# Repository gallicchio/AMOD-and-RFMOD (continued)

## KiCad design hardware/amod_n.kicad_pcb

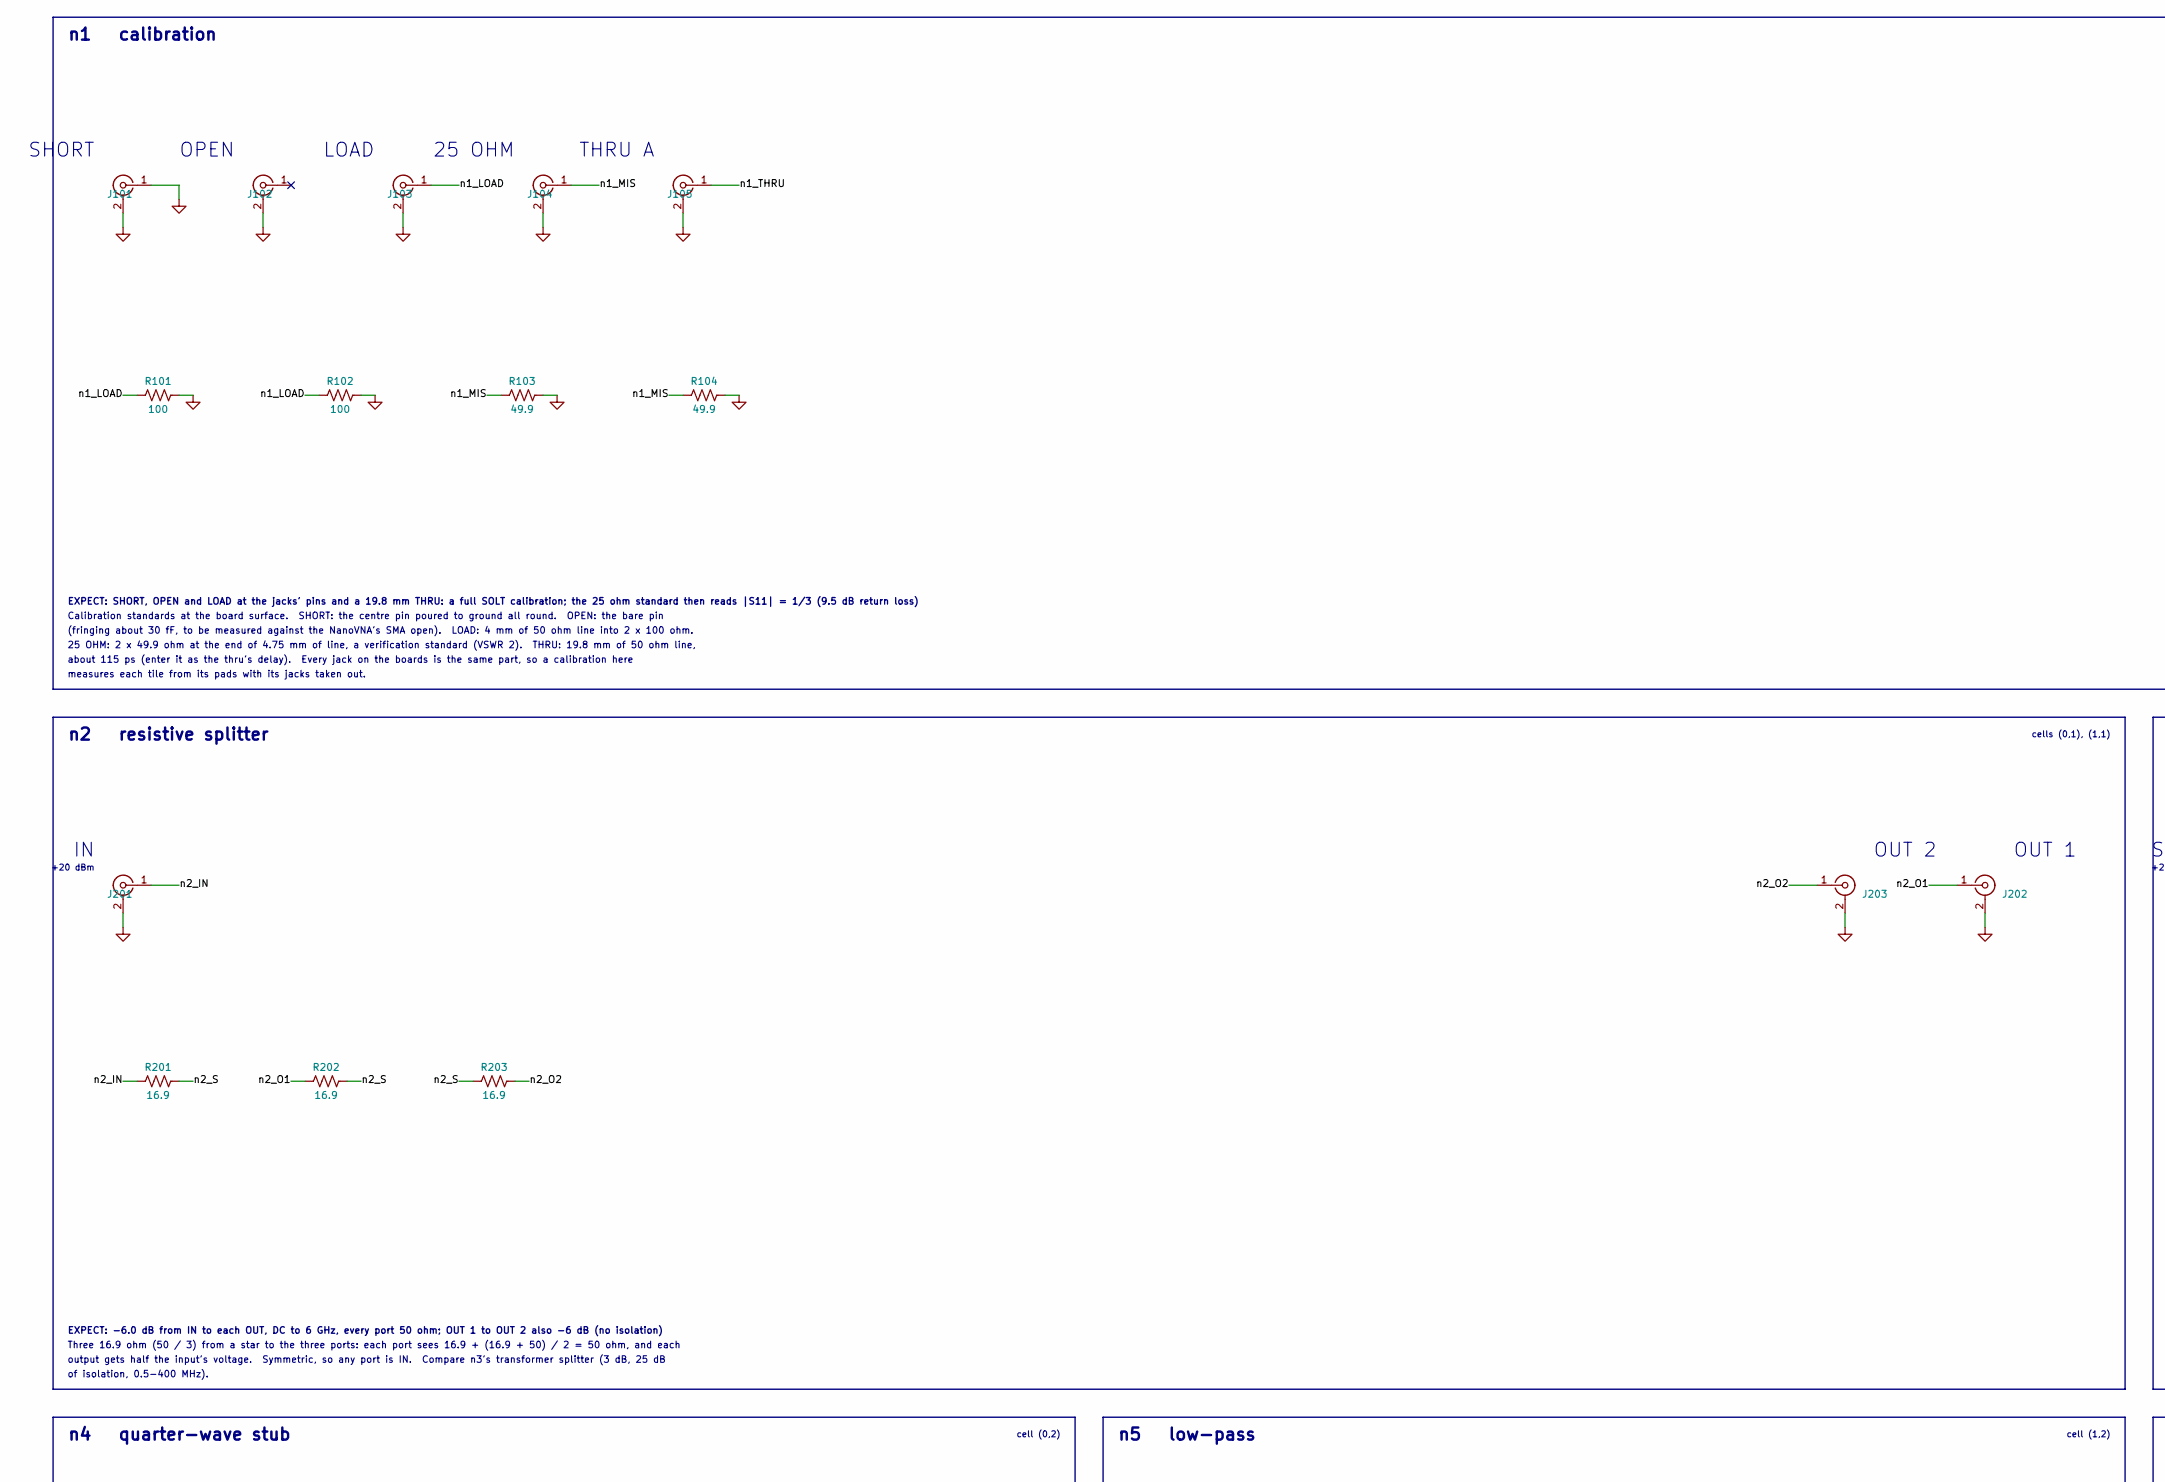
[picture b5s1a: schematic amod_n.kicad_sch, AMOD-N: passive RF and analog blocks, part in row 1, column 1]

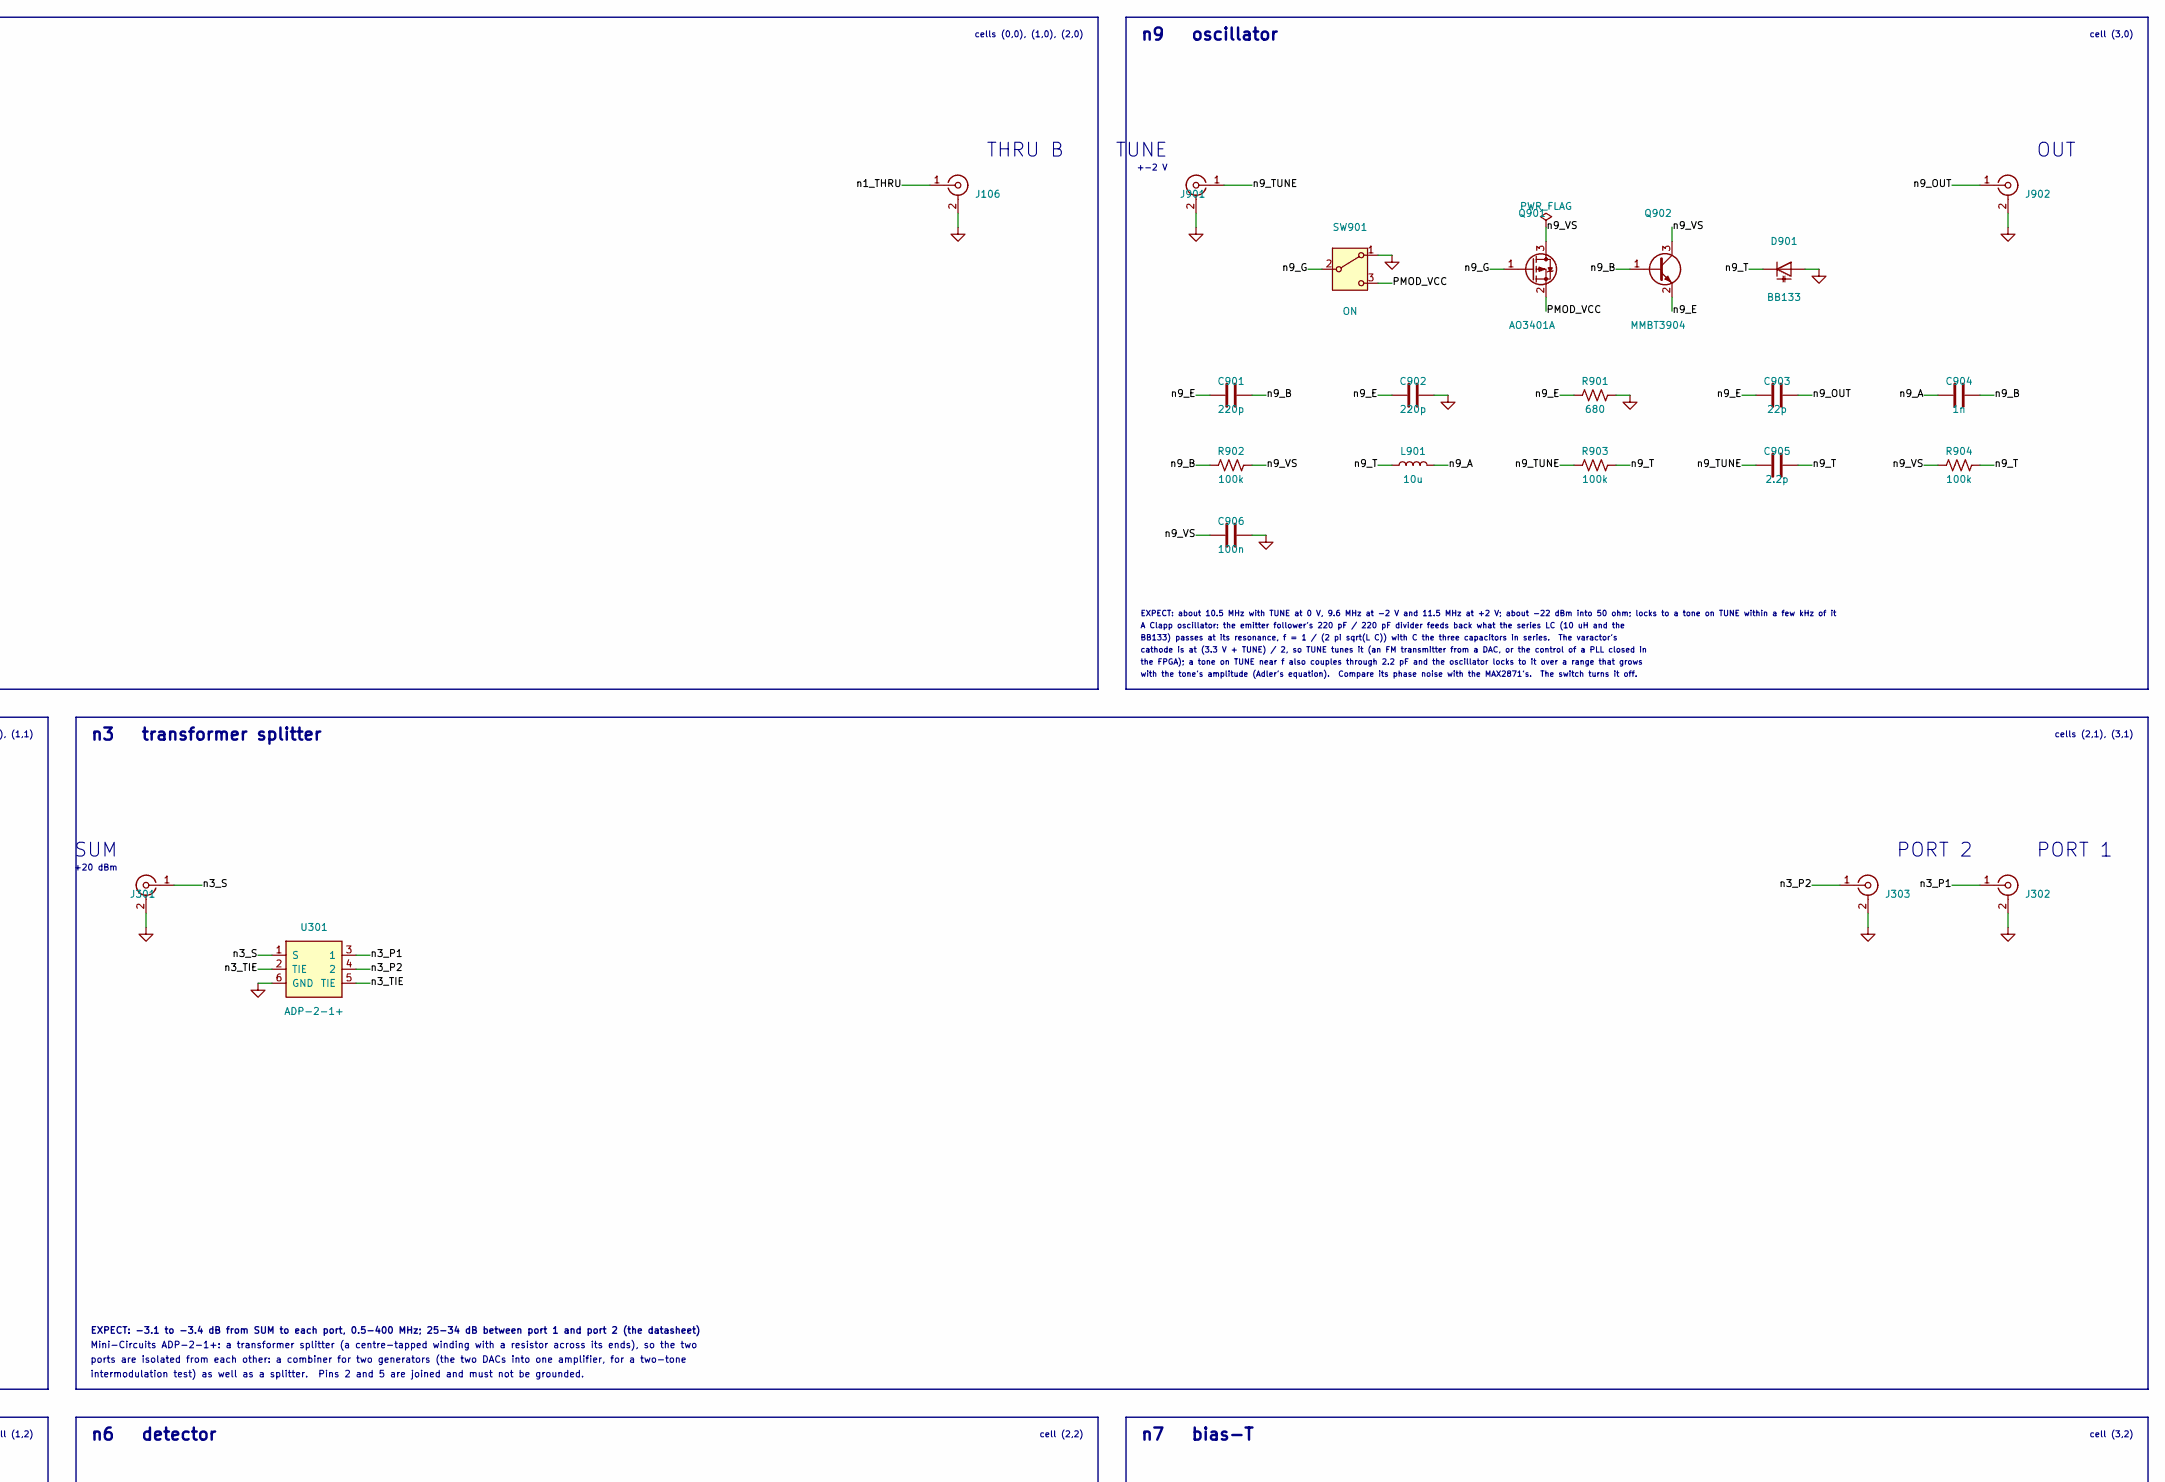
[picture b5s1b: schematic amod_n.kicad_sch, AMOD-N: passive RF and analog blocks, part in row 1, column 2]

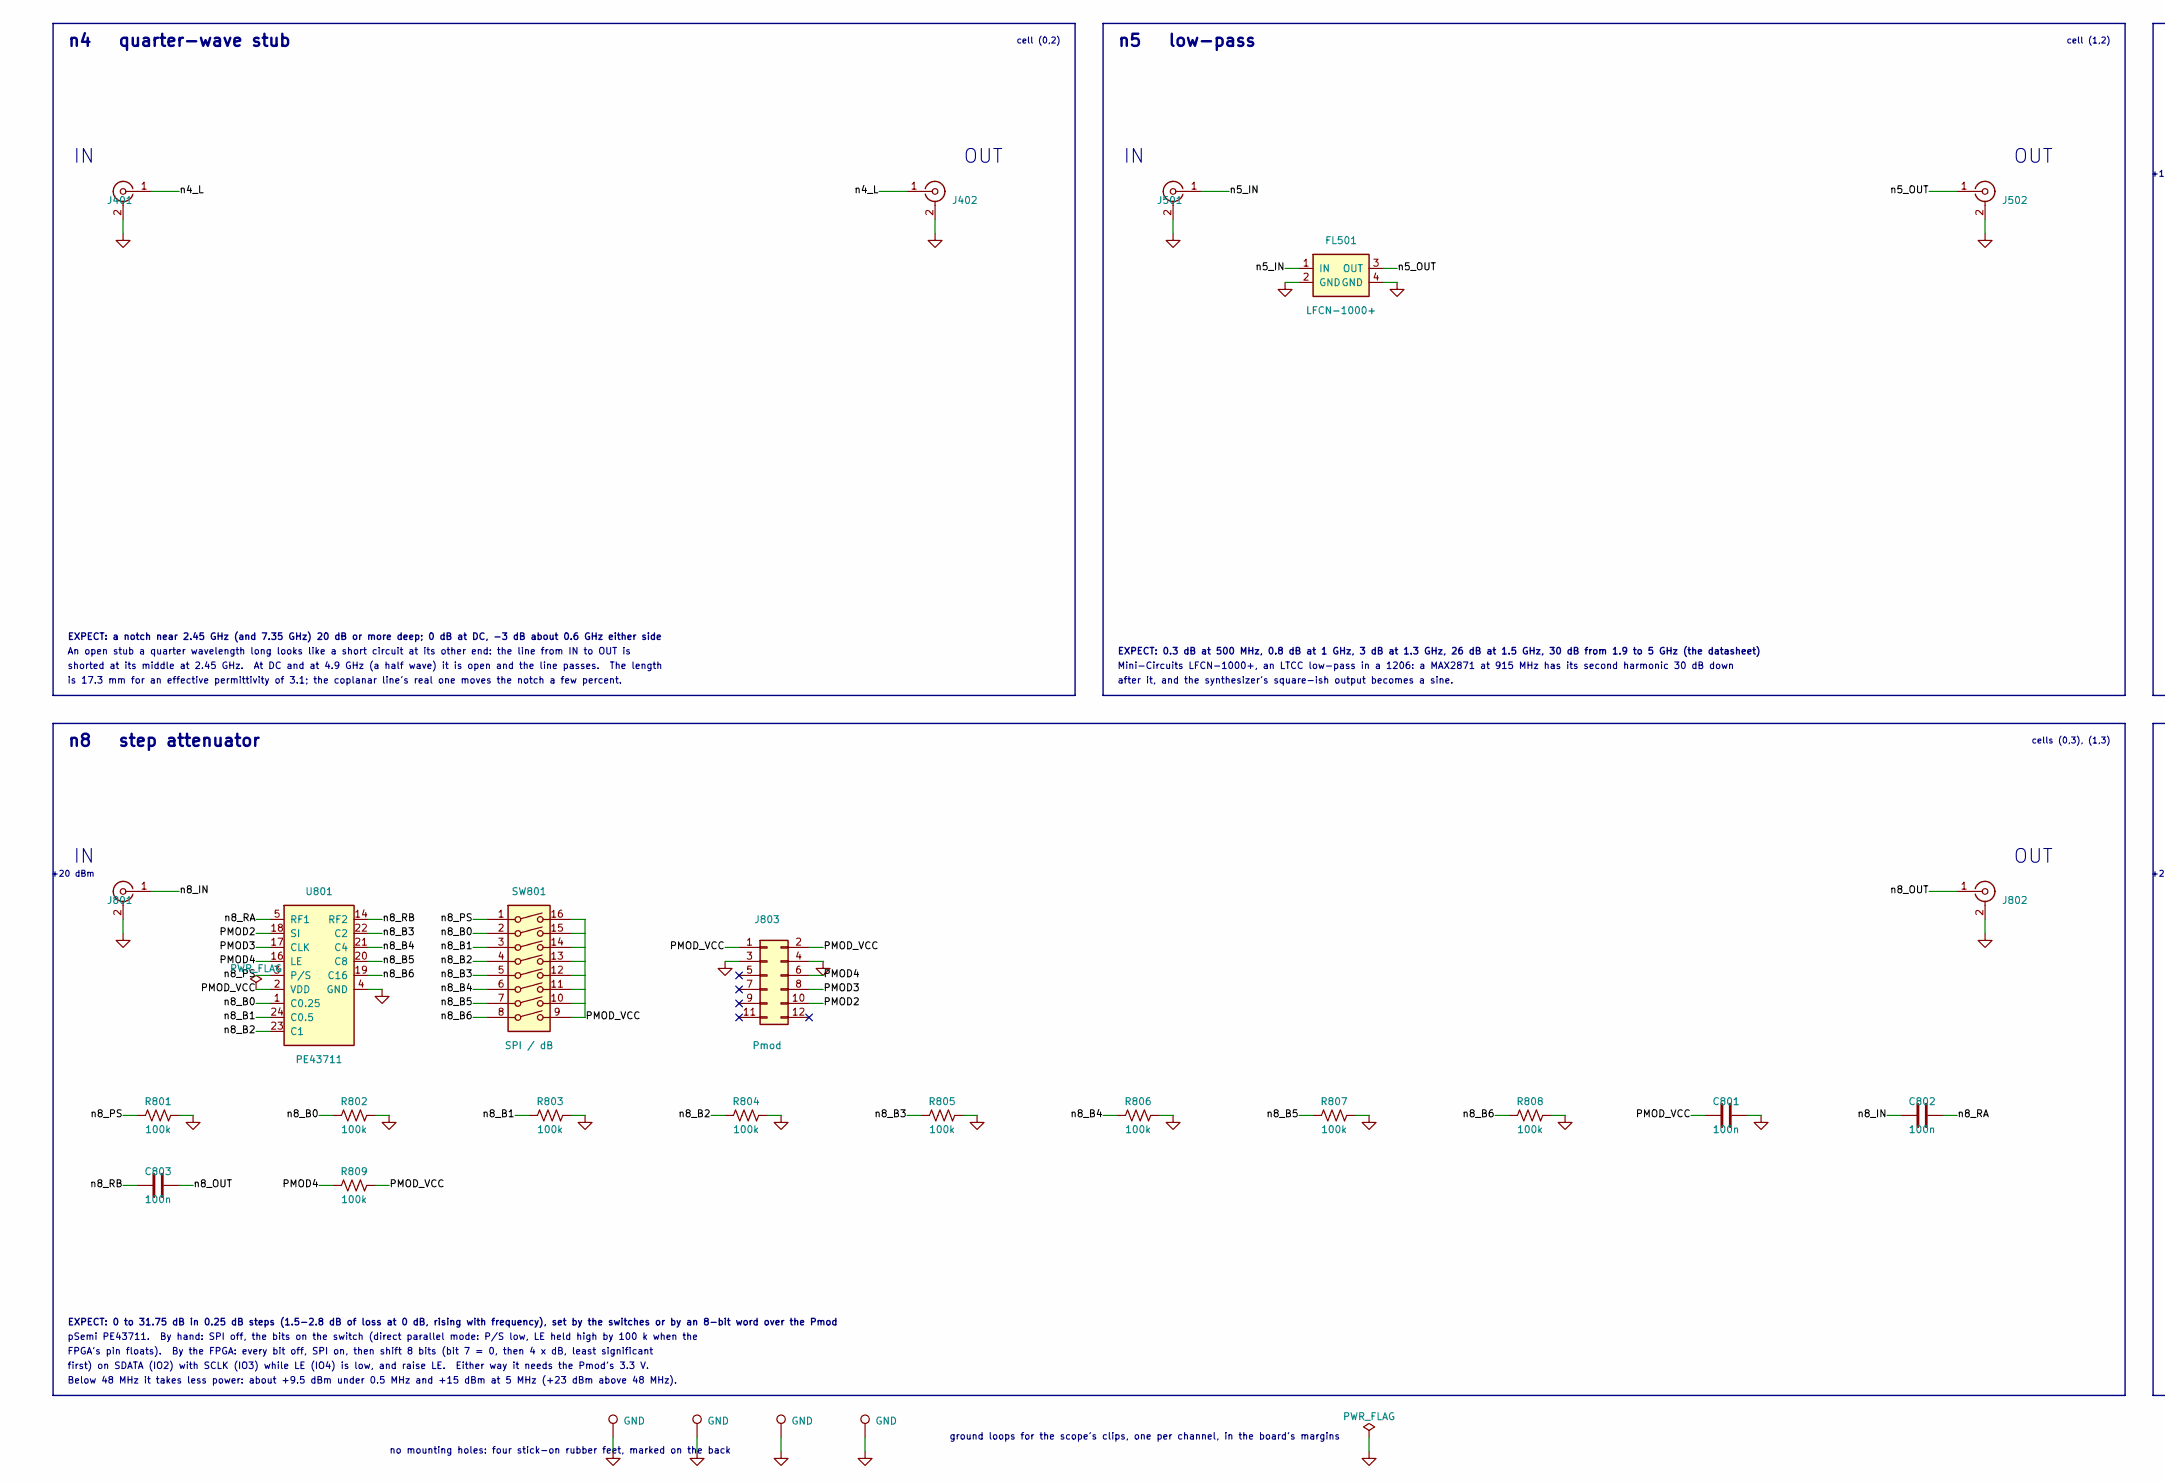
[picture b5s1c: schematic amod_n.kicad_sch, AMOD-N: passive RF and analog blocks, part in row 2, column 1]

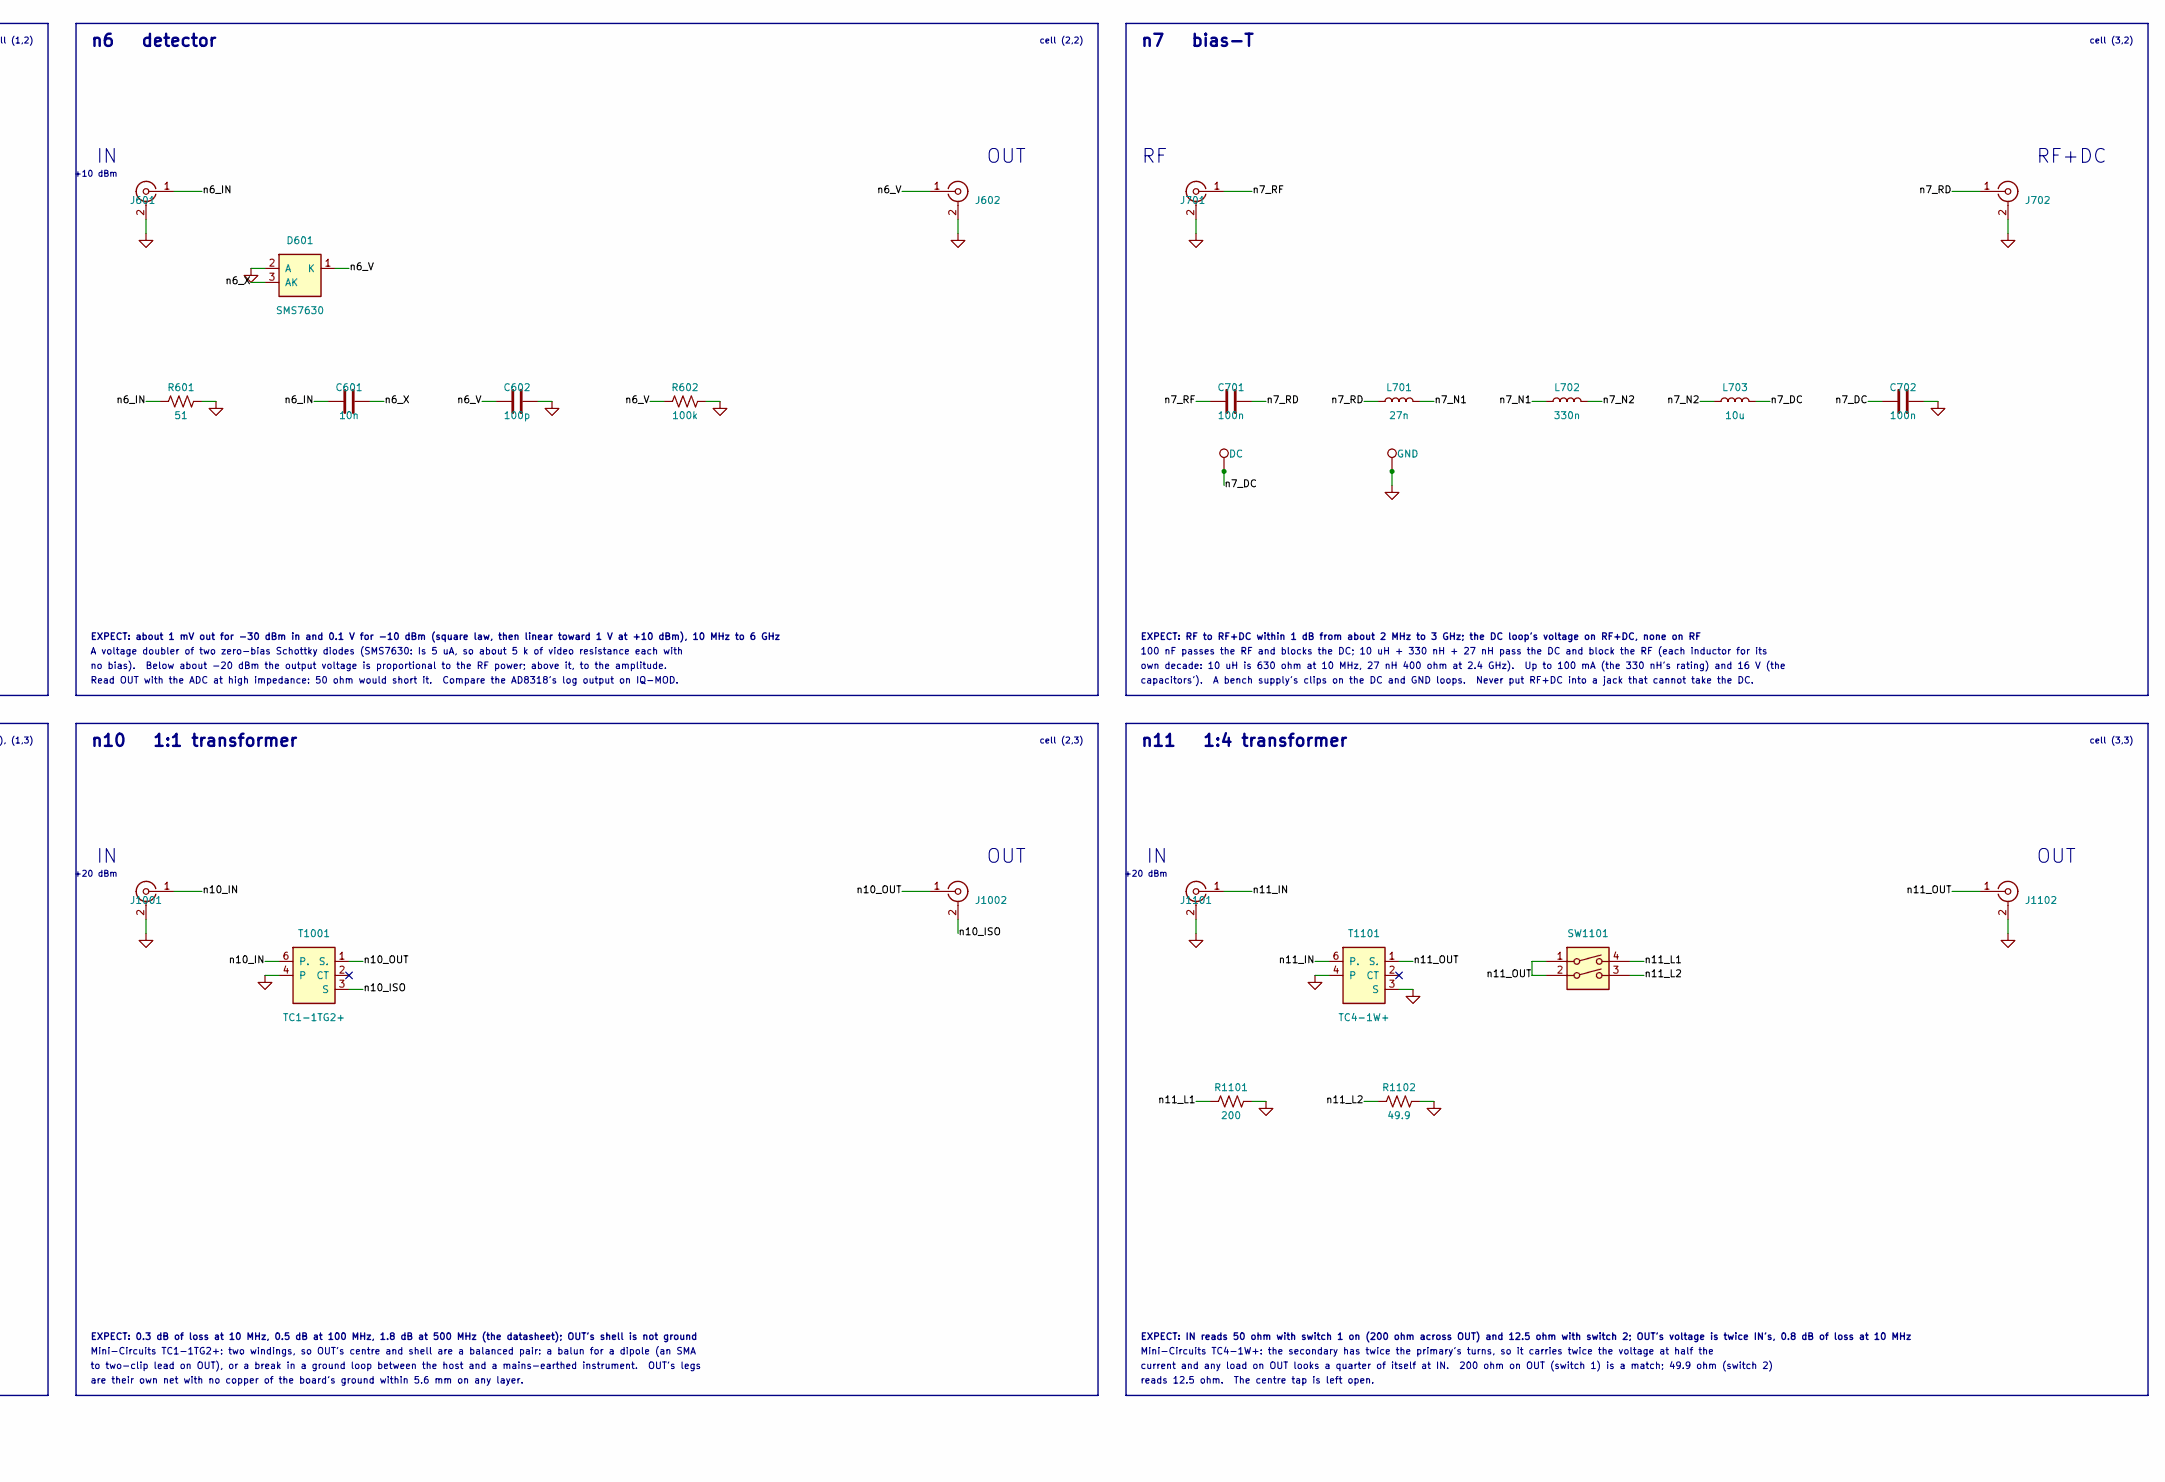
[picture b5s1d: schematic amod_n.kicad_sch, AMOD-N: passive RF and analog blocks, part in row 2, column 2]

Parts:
C601: 10n; C_0402_1005Metric; MPN CL05B103KB5NNNC; LCSC C15195
C602: 100p; C_0402_1005Metric; MPN 0402CG101J500NT; LCSC C1546
C701, C702, C801, C802, C803, C906: 100n; C_0402_1005Metric; MPN CL05B104KO5NNNC; LCSC C1525
C901, C902: 220p; C_0402_1005Metric; MPN 0402CG221J500NT; LCSC C39122
C903: 22p; C_0402_1005Metric; MPN 0402CG220J500NT; LCSC C1555
C904: 1n; C_0402_1005Metric; MPN 0402B102K500NT; LCSC C1523
C905: 2.2p; C_0402_1005Metric; MPN 0402CG2R2C500NT; LCSC C1559
D601: SMS7630; SOT-23; MPN SMS7630-006LF; LCSC C6489012
D901: BB133; D_SOD-323; MPN BB133; LCSC C5334579
FL501: LFCN-1000+; Filter_LTCC_1206_LFCN; MPN LFCN-1000+; LCSC C879868
J101, J102, J103, J104, J105, J106, J201, J202, J203, J301, J302, J303, J401, J402, J501, J502, J601, J602, J701, J702, J801, J802, J901, J902, J1001, J1002, J1101, J1102: SMA; SMA_BWSMA-KE-Z001_Vertical; MPN BWSMA-KE-Z001; LCSC C496549
J803: Pmod; PinHeader_2x06_P2.54mm_Horizontal_PZ254R-12-12P; MPN PZ254R-12-12P; LCSC C492434
L701: 27n; L_0402_1005Metric; MPN LQW15AN27NG80D; LCSC C882469
L702: 330n; L_0603_1608Metric; MPN CS0603-R33J-S; LCSC C142165
L703, L901: 10u; L_1210_3225Metric; MPN NLV32T-100J-PF; LCSC C76835
Q901: AO3401A; SOT-23; MPN AO3401A; LCSC C15127
Q902: MMBT3904; SOT-23; MPN MMBT3904(RANGE:100-300); LCSC C20526
R101, R102: 100; R_0402_1005Metric; MPN 0402WGF1000TCE; LCSC C25076
R103, R104, R1102: 49.9; R_0402_1005Metric; MPN CRCW040249R9FKEDHP; LCSC C844112
R201, R202, R203: 16.9; R_0402_1005Metric; MPN 0402WGF169JTCE; LCSC C82287
R601: 51; R_0402_1005Metric; MPN 0402WGF510JTCE; LCSC C25125
R602, R801, R802, R803, R804, R805, R806, R807, R808, R809, R902, R903, R904: 100k; R_0402_1005Metric; MPN 0402WGF1003TCE; LCSC C25741
R901: 680; R_0402_1005Metric; MPN 0402WGF6800TCE; LCSC C25130
R1101: 200; R_0402_1005Metric; MPN 0402WGF2000TCE; LCSC C25087
SW801: SPI / dB; SW_DIP_SPSTx08_Slide_1.27mm_DSHP08; MPN DSHP08TSGET; LCSC C40738
SW901: ON; SW_SPDT_Shouhan_MSK12C02; MPN MSK12C02; LCSC C431540
SW1101: LOAD; SW_DIP_SPSTx02_Slide_1.27mm_DSHP02; MPN DSHP02TSGET; LCSC C40735
T1001: TC1-1TG2+; MiniCircuits_AT224_5P; MPN TC1-1TG2+; LCSC C3305009
T1101: TC4-1W+; MiniCircuits_AT224_5P; MPN TC4-1W+; LCSC C879855
TP701: DC; TestPoint_Loop_RH-5019; MPN RH-5019; LCSC C5199800
TP702, TP9901, TP9902, TP9903, TP9904: GND; TestPoint_Loop_RH-5019; MPN RH-5019; LCSC C5199800
U301: ADP-2-1+; MiniCircuits_CD636_ADP-2-1; MPN ADP-2-1+; LCSC C2683460
U801: PE43711; QFN-24-1EP_4x4mm_P0.5mm_EP2.7x2.7mm; MPN PE43711B-Z; LCSC C470929

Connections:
/PMOD2: J803.10, U801.18 (SI)
/PMOD3: J803.8, U801.17 (CLK)
/PMOD4: J803.6, R809.1, U801.16 (LE)
/PMOD_VCC: C801.1, J803.1, J803.2, Q901.2 (S), R809.2, SW801.9, SW801.10, SW801.11, SW801.12, SW801.13, SW801.14, SW801.15, SW801.16, SW901.3 (C), U801.2 (VDD)
/n1_LOAD: J103.1 (In), R101.1, R102.1
/n1_MIS: J104.1 (In), R103.1, R104.1
/n1_THRU: J105.1 (In), J106.1 (In)
/n2_IN: J201.1 (In), R201.1
/n2_O1: J202.1 (In), R202.1
/n2_O2: J203.1 (In), R203.2
/n2_S: R201.2, R202.2, R203.1
/n3_P1: J302.1 (In), U301.3 (1)
/n3_P2: J303.1 (In), U301.4 (2)
/n3_S: J301.1 (In), U301.1 (S)
/n3_TIE: U301.2 (TIE), U301.5 (TIE)
/n4_L: J401.1 (In), J402.1 (In)
/n5_IN: FL501.1 (IN), J501.1 (In)
/n5_OUT: FL501.3 (OUT), J502.1 (In)
/n6_IN: C601.1, J601.1 (In), R601.1
/n6_V: C602.1, D601.1 (K), J602.1 (In), R602.1
/n6_X: C601.2, D601.3 (AK)
/n7_DC: C702.1, L703.2, TP701.1
/n7_N1: L701.2, L702.1
/n7_N2: L702.2, L703.1
/n7_RD: C701.2, J702.1 (In), L701.1
/n7_RF: C701.1, J701.1 (In)
/n8_B0: R802.1, SW801.2, U801.1 (C0.25)
/n8_B1: R803.1, SW801.3, U801.24 (C0.5)
/n8_B2: R804.1, SW801.4, U801.23 (C1)
/n8_B3: R805.1, SW801.5, U801.22 (C2)
/n8_B4: R806.1, SW801.6, U801.21 (C4)
/n8_B5: R807.1, SW801.7, U801.20 (C8)
/n8_B6: R808.1, SW801.8, U801.19 (C16)
/n8_IN: C802.1, J801.1 (In)
/n8_OUT: C803.2, J802.1 (In)
/n8_PS: R801.1, SW801.1, U801.3 (P/S)
/n8_RA: C802.2, U801.5 (RF1)
/n8_RB: C803.1, U801.14 (RF2)
/n9_A: C904.1, L901.2
/n9_B: C901.2, C904.2, Q902.1 (B), R902.1
/n9_E: C901.1, C902.1, C903.1, Q902.2 (E), R901.1
/n9_G: Q901.1 (G), SW901.2 (B)
/n9_OUT: C903.2, J902.1 (In)
/n9_T: C905.2, D901.1 (K), L901.1, R903.2, R904.2
/n9_TUNE: C905.1, J901.1 (In), R903.1
/n9_VS: C906.1, Q901.3 (D), Q902.3 (C), R902.2, R904.1
/n10_IN: J1001.1 (In), T1001.6 (P.)
/n10_ISO: J1002.2 (Ext), T1001.3 (S)
/n10_OUT: J1002.1 (In), T1001.1 (S.)
/n11_IN: J1101.1 (In), T1101.6 (P.)
/n11_L1: R1101.1, SW1101.4
/n11_L2: R1102.1, SW1101.3
/n11_OUT: J1102.1 (In), SW1101.1, SW1101.2, T1101.1 (S.)
GND: C602.2, C702.2, C801.2, C902.2, C906.2, D601.2 (A), D901.2 (A), FL501.2 (GND), FL501.4 (GND), J101.1 (In), J101.2 (Ext), J102.2 (Ext), J103.2 (Ext), J104.2 (Ext), J105.2 (Ext), J106.2 (Ext), J201.2 (Ext), J202.2 (Ext), J203.2 (Ext), J301.2 (Ext), J302.2 (Ext), J303.2 (Ext), J401.2 (Ext), J402.2 (Ext), J501.2 (Ext), J502.2 (Ext), J601.2 (Ext), J602.2 (Ext), J701.2 (Ext), J702.2 (Ext), J801.2 (Ext), J802.2 (Ext), J803.3, J803.4, J901.2 (Ext), J902.2 (Ext), J1001.2 (Ext), J1101.2 (Ext), J1102.2 (Ext), R101.2, R102.2, R103.2, R104.2, R601.2, R602.2, R801.2, R802.2, R803.2, R804.2, R805.2, R806.2, R807.2, R808.2, R901.2, R1101.2, R1102.2, SW901.1 (A), T1001.4, T1101.3 (S), T1101.4, TP702.1, TP9901.1, TP9902.1, TP9903.1, TP9904.1, U301.6 (GND), U801.4 (GND), U801.6 (GND), U801.7 (GND), U801.8 (GND), U801.9 (GND), U801.10 (GND), U801.11 (GND), U801.12 (GND), U801.13 (GND), U801.15 (GND), U801.25 (GND)

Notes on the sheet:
SUM
cells (2,1), (3,1)
EXPECT: -3.1 to -3.4 dB from SUM to each port, 0.5-400 MHz; 25-34 dB between port 1 and port 2 (the datasheet)
OUT
EXPECT: 0.3 dB of loss at 10 MHz, 0.5 dB at 100 MHz, 1.8 dB at 500 MHz (the datasheet); OUT's shell is not ground
EXPECT: 0 to 31.75 dB in 0.25 dB steps (1.5-2.8 dB of loss at 0 dB, rising with frequency), set by the switches or by an 8-bit word over the Pmod
n1 calibration
cells (0,0), (1,0), (2,0)
n3 transformer splitter
cell (0,2)
measures each tile from its pads with its jacks taken out.
RF+DC
25 OHM: 2 x 49.9 ohm at the end of 4.75 mm of line, a verification standard (VSWR 2). THRU: 19.8 mm of 50 ohm line,
n11 1:4 transformer
cell (3,3)
An open stub a quarter wavelength long looks like a short circuit at its other end: the line from IN to OUT is
(fringing about 30 fF, to be measured against the NanoVNA's SMA open). LOAD: 4 mm of 50 ohm line into 2 x 100 ohm.
25 OHM
PORT 2
A voltage doubler of two zero-bias Schottky diodes (SMS7630: Is 5 uA, so about 5 k of video resistance each with
OUT 2
THRU A
+20 dBm
n2 resistive splitter
EXPECT: SHORT, OPEN and LOAD at the jacks' pins and a 19.8 mm THRU: a full SOLT calibration; the 25 ohm standard then reads |S11| = 1/3 (9.5 dB return loss)
LOAD
n8 step attenuator
the FPGA); a tone on TUNE near f also couples through 2.2 pF and the oscillator locks to it over a range that grows
EXPECT: RF to RF+DC within 1 dB from about 2 MHz to 3 GHz; the DC loop's voltage on RF+DC, none on RF
are their own net with no copper of the board's ground within 5.6 mm on any layer.
of isolation, 0.5-400 MHz).
current and any load on OUT looks a quarter of itself at IN. 200 ohm on OUT (switch 1) is a match; 49.9 ohm (switch 2)
EXPECT: a notch near 2.45 GHz (and 7.35 GHz) 20 dB or more deep; 0 dB at DC, -3 dB about 0.6 GHz either side
EXPECT: -6.0 dB from IN to each OUT, DC to 6 GHz, every port 50 ohm; OUT 1 to OUT 2 also -6 dB (no isolation)
no bias). Below about -20 dBm the output voltage is proportional to the RF power; above it, to the amplitude.
n5 low-pass
cell (2,3)
capacitors'). A bench supply's clips on the DC and GND loops. Never put RF+DC into a jack that cannot take the DC.
EXPECT: about 1 mV out for -30 dBm in and 0.1 V for -10 dBm (square law, then linear toward 1 V at +10 dBm), 10 MHz to 6 GHz
Mini-Circuits ADP-2-1+: a transformer splitter (a centre-tapped winding with a resistor across its ends), so the two

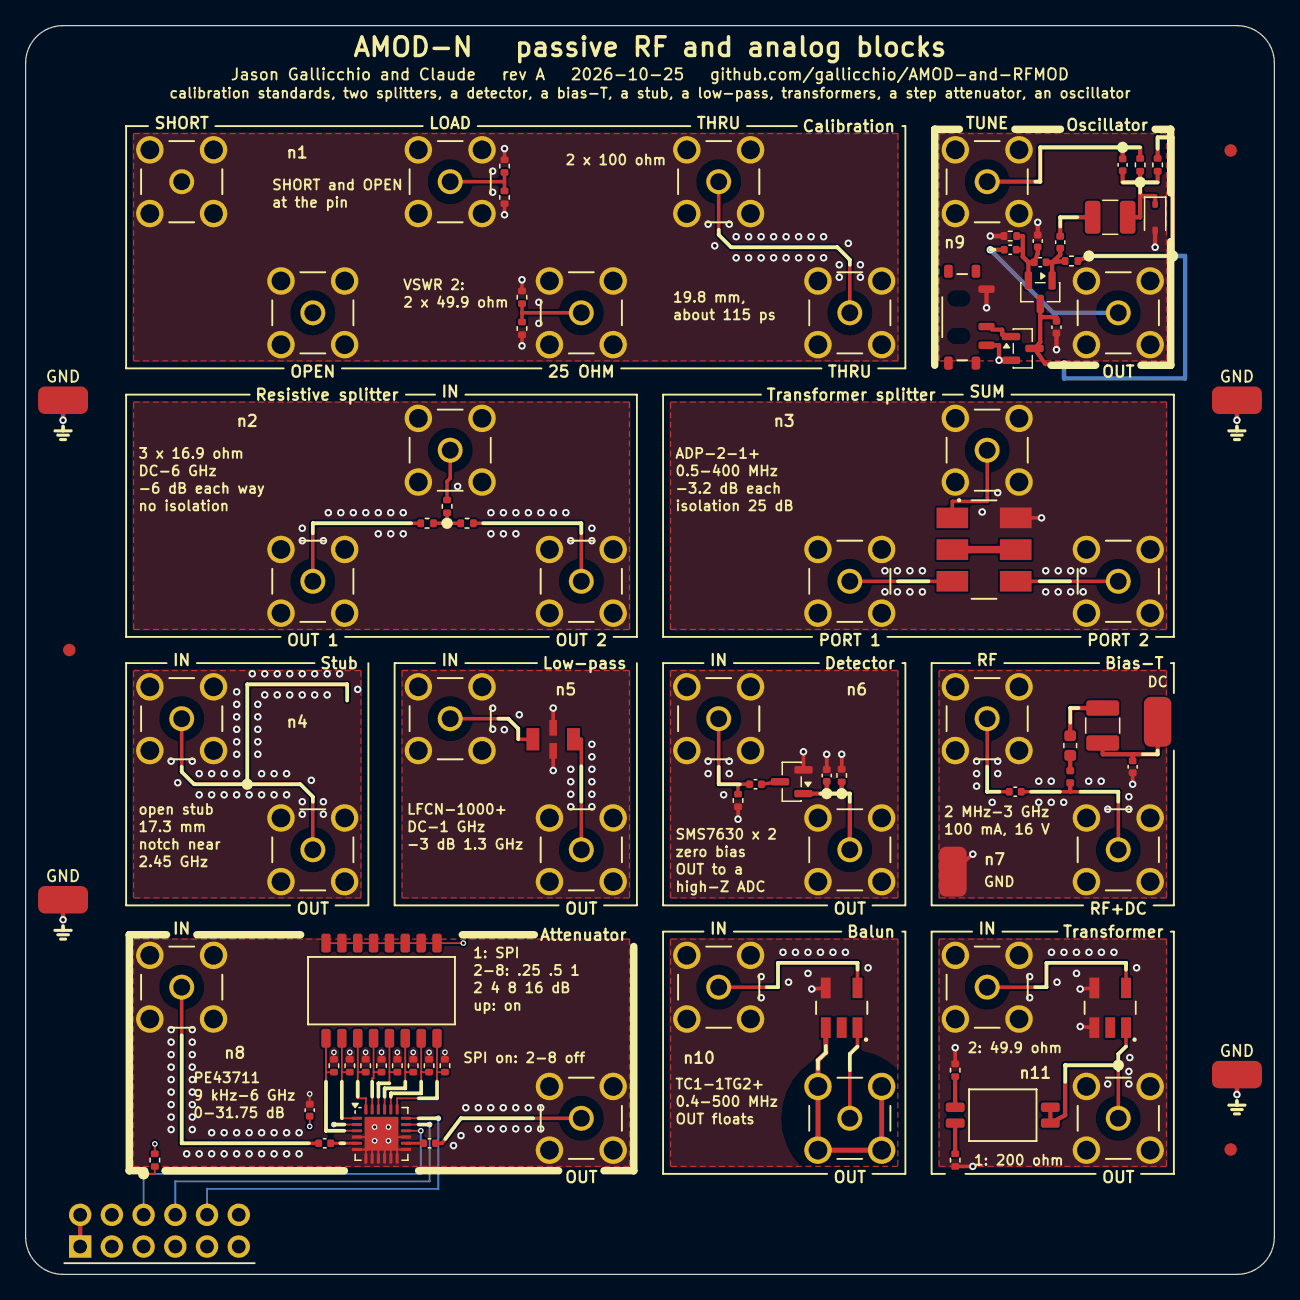
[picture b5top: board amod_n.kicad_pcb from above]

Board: 4 copper layers, 100.0 x 100.0 mm, 88 parts (0 on the bottom side), 54 nets.
